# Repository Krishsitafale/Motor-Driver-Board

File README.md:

# TeleOps Motor Driver PCB
### International Rover Challenge (IRC) 2026 | Team Vishwa, VJTI

## Overview

The **TeleOps Motor Driver PCB** is a custom-designed embedded motor control board developed for **Team Vishwa, VJTI** for the **International Rover Challenge (IRC) 2026**.

The objective of this board was to consolidate multiple motor driver modules, PWM generators, power regulators, and peripheral interfaces into a single reliable PCB capable of controlling the rover's complete teleoperation subsystem.

Unlike conventional rover electronics that rely on several separate modules connected with extensive wiring, this PCB integrates all essential electronics into one compact system, improving reliability, reducing wiring complexity, and simplifying maintenance during competitions.

## Features

- ESP32-S3 based control unit
- Custom 5V Buck Converter (TPS54302)
- 10 High Current H-Bridge Drivers (BTN9970LV)
- PCA9685 16-Channel PWM Expander
- Encoder Interfaces
- GPS Interface
- Servo Motor Support
- Modular Connectors
- High Current PCB Layout
- Designed specifically for IRC Rover

## Hardware Specifications

| Component | Description |
|-----------|-------------|
| Microcontroller | ESP32-S3 |
| Buck Converter | TPS54302 |
| Motor Driver  | BTN9970LV |
| PWM Expansion | PCA9685 |
| Logic Voltage | 3.3V |
| Motor Supply  | 12V |
| PCB | 2 Layer |
| Communication | I²C, GPIO, PWM |

# System Architecture

                         12V Battery
                              │
                ┌─────────────┴─────────────┐
                │                           │
                │                    Motor Supply
                │                           │
                ▼                           ▼
      TPS54302 Buck Converter      10× BTN9970LV Drivers
                │
                ▼
             5V Rail
                │
                ▼
           ESP32-S3 MCU
                │
      ┌─────────┼─────────────────────────────┐
      │         │                             │
      │         │ I²C                         │ Native PWM
      │         ▼                             ▼
      │     PCA9685                    ESP32 PWM Outputs
      │   (16 Channel PWM)             (LEDC Peripheral)
      │         │                             │
      │         │                             ├──────── 2 DC Motor Drivers
      │         │                             │
      │         │                             └──────── 4 Servo Motors
      │         │
      │         ├──────── 8 Motor Driver PWM Inputs
      │         │
      │         └──────── Future Expansion
      │
      ├──────── Encoder Inputs
      │
      ├──────── GPS Interface
      │
      └──────── Programming Interface

## Motor Control Architecture

The rover requires control of multiple actuators with independent PWM channels. To efficiently utilize the ESP32's peripherals, the PWM generation is divided as follows:

| PWM Source | Devices Controlled |
|------------|--------------------|
| PCA9685(PWM Expander) | 8 High-Power DC Motor Drivers |
| ESP32 Native PWM      | 2 High-Power DC Motor Drivers |
| ESP32 Native PWM      | 4 Servo Motors                |

This hybrid architecture reduces the processing load on the ESP32 while providing highly stable PWM signals for the drivetrain and robotic arm.

## Supported Actuators

### Drive System

- 6 Planetary DC Motors

### Robotic Arm

- 3 Stepper Motors
- 1 Planetary DC Motor
- 2 Worm Gear Motors
- 4 Servo Motors

### Sensors

- OE775 Quadrature Encoders
- GPS Module

## PCB Highlights

- Dedicated power plane for motor supply
- Optimized ground routing
- High-current copper traces
- Decoupling for every IC
- Modular connector layout
- Compact footprint
- Easy debugging headers
- Competition-ready wiring

## Testing

The PCB has successfully passed the following validation tests.

- Power Supply Verification
- ESP32 Programming
- Buck Converter Efficiency Test
- PCA9685 Communication
- PWM Signal Verification
- Motor Driver Validation
- Encoder Testing
- Servo Testing
- Thermal Performance
- Complete System Integration

## Future Improvements

- Closed Loop Motor Control
- Current Monitoring
- Battery Voltage Monitoring
- CAN Bus Support
- IMU Integration
- OTA Firmware Updates
- ROS 2 Compatibility

## Gallery

## Acknowledgements

This PCB was designed and developed as part of the **Electronics Subsystem** of **Team Vishwa, VJTI** for the **International Rover Challenge (IRC) 2026**.

Special thanks to **Atharva Khare** for his invaluable guidance throughout the design, debugging, and testing phases of the project.

## Author

**Krish Sitafale**

Electronics & Telecommunication Engineering  
Veermata Jijabai Technological Institute (VJTI), Mumbai

Team Vishwa – IRC 2026

## License

This project is released for educational and research purposes.

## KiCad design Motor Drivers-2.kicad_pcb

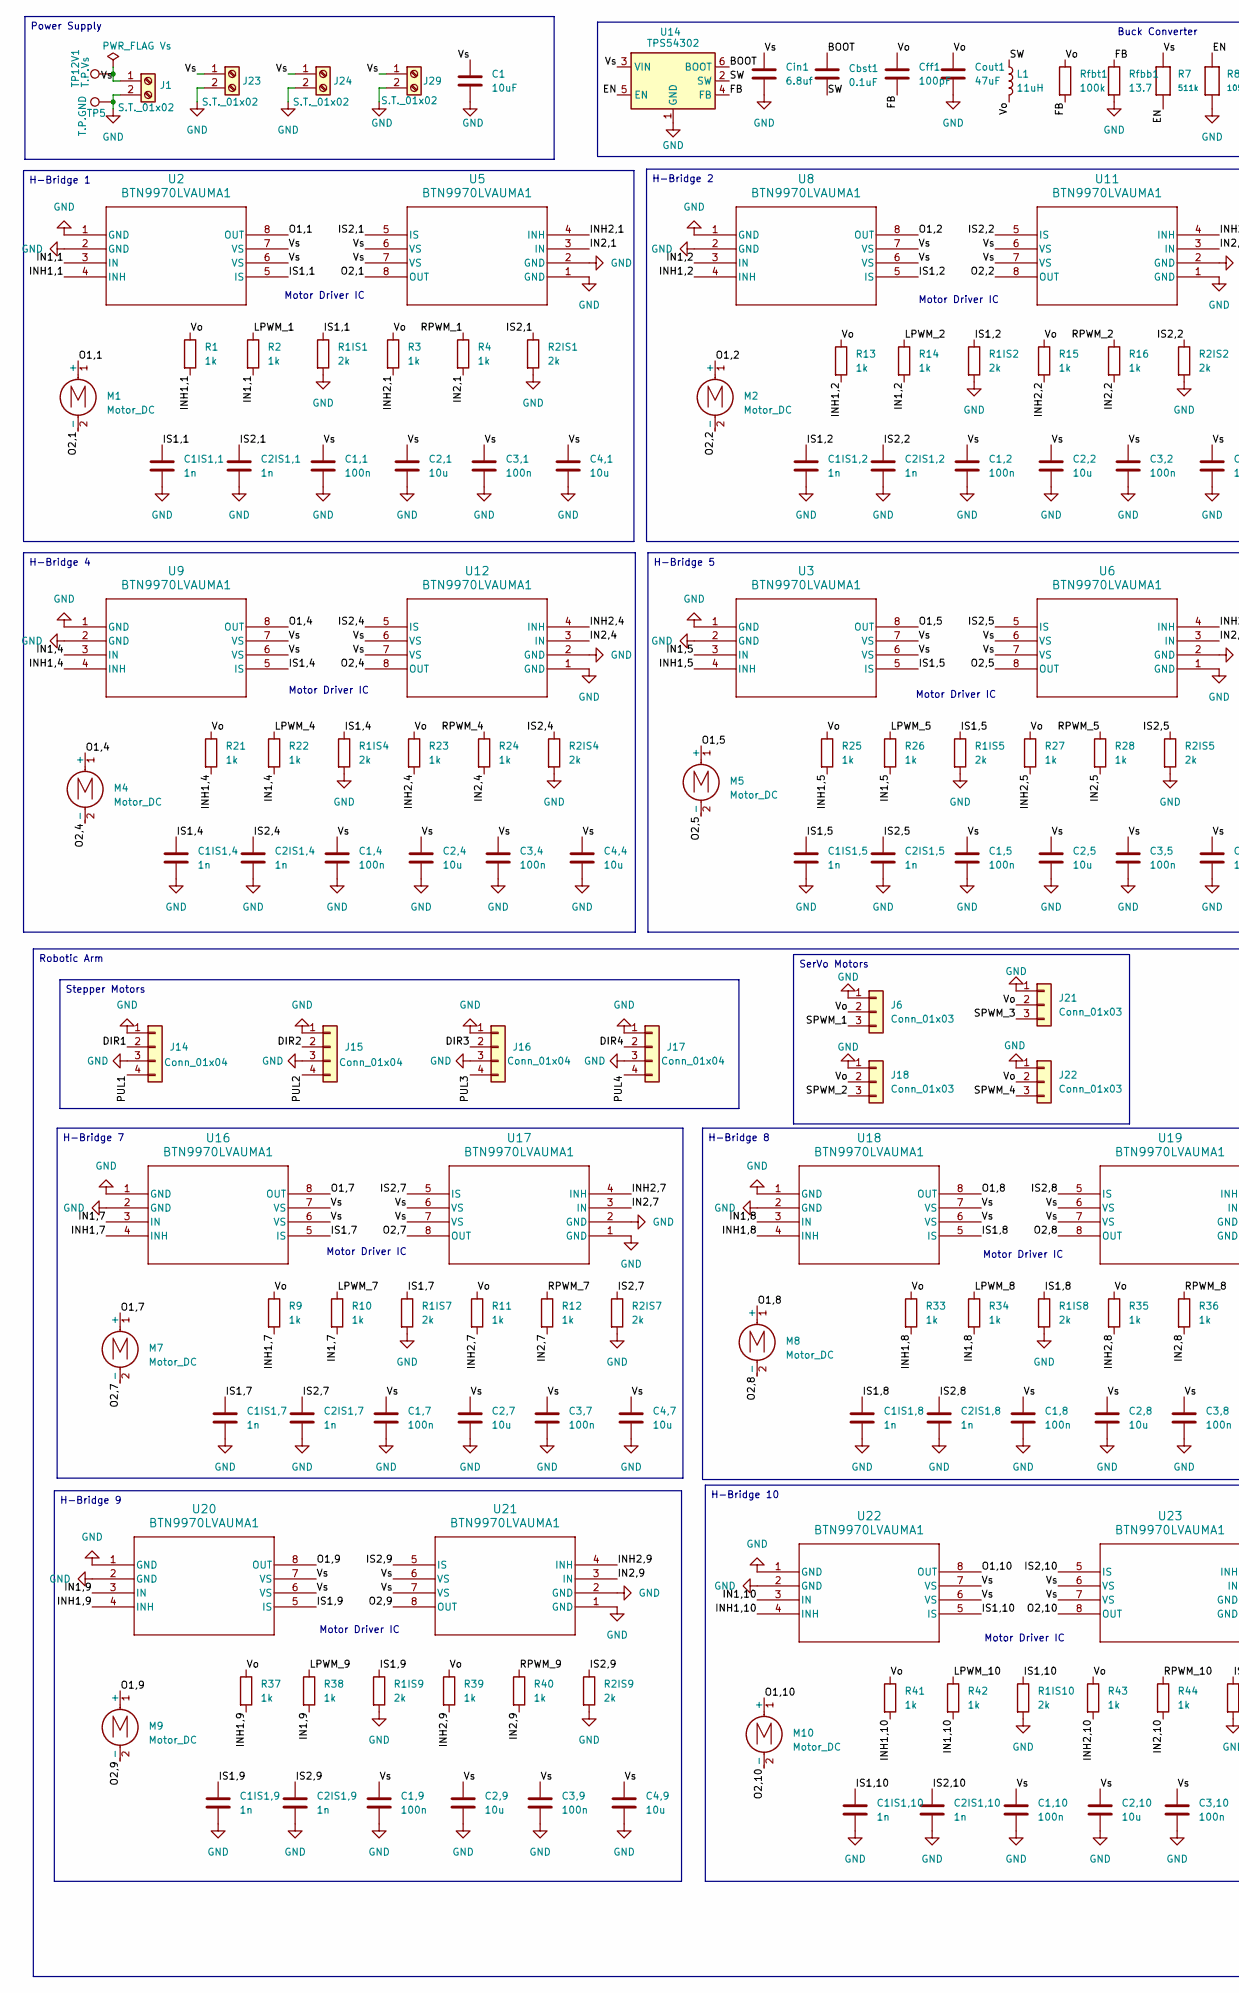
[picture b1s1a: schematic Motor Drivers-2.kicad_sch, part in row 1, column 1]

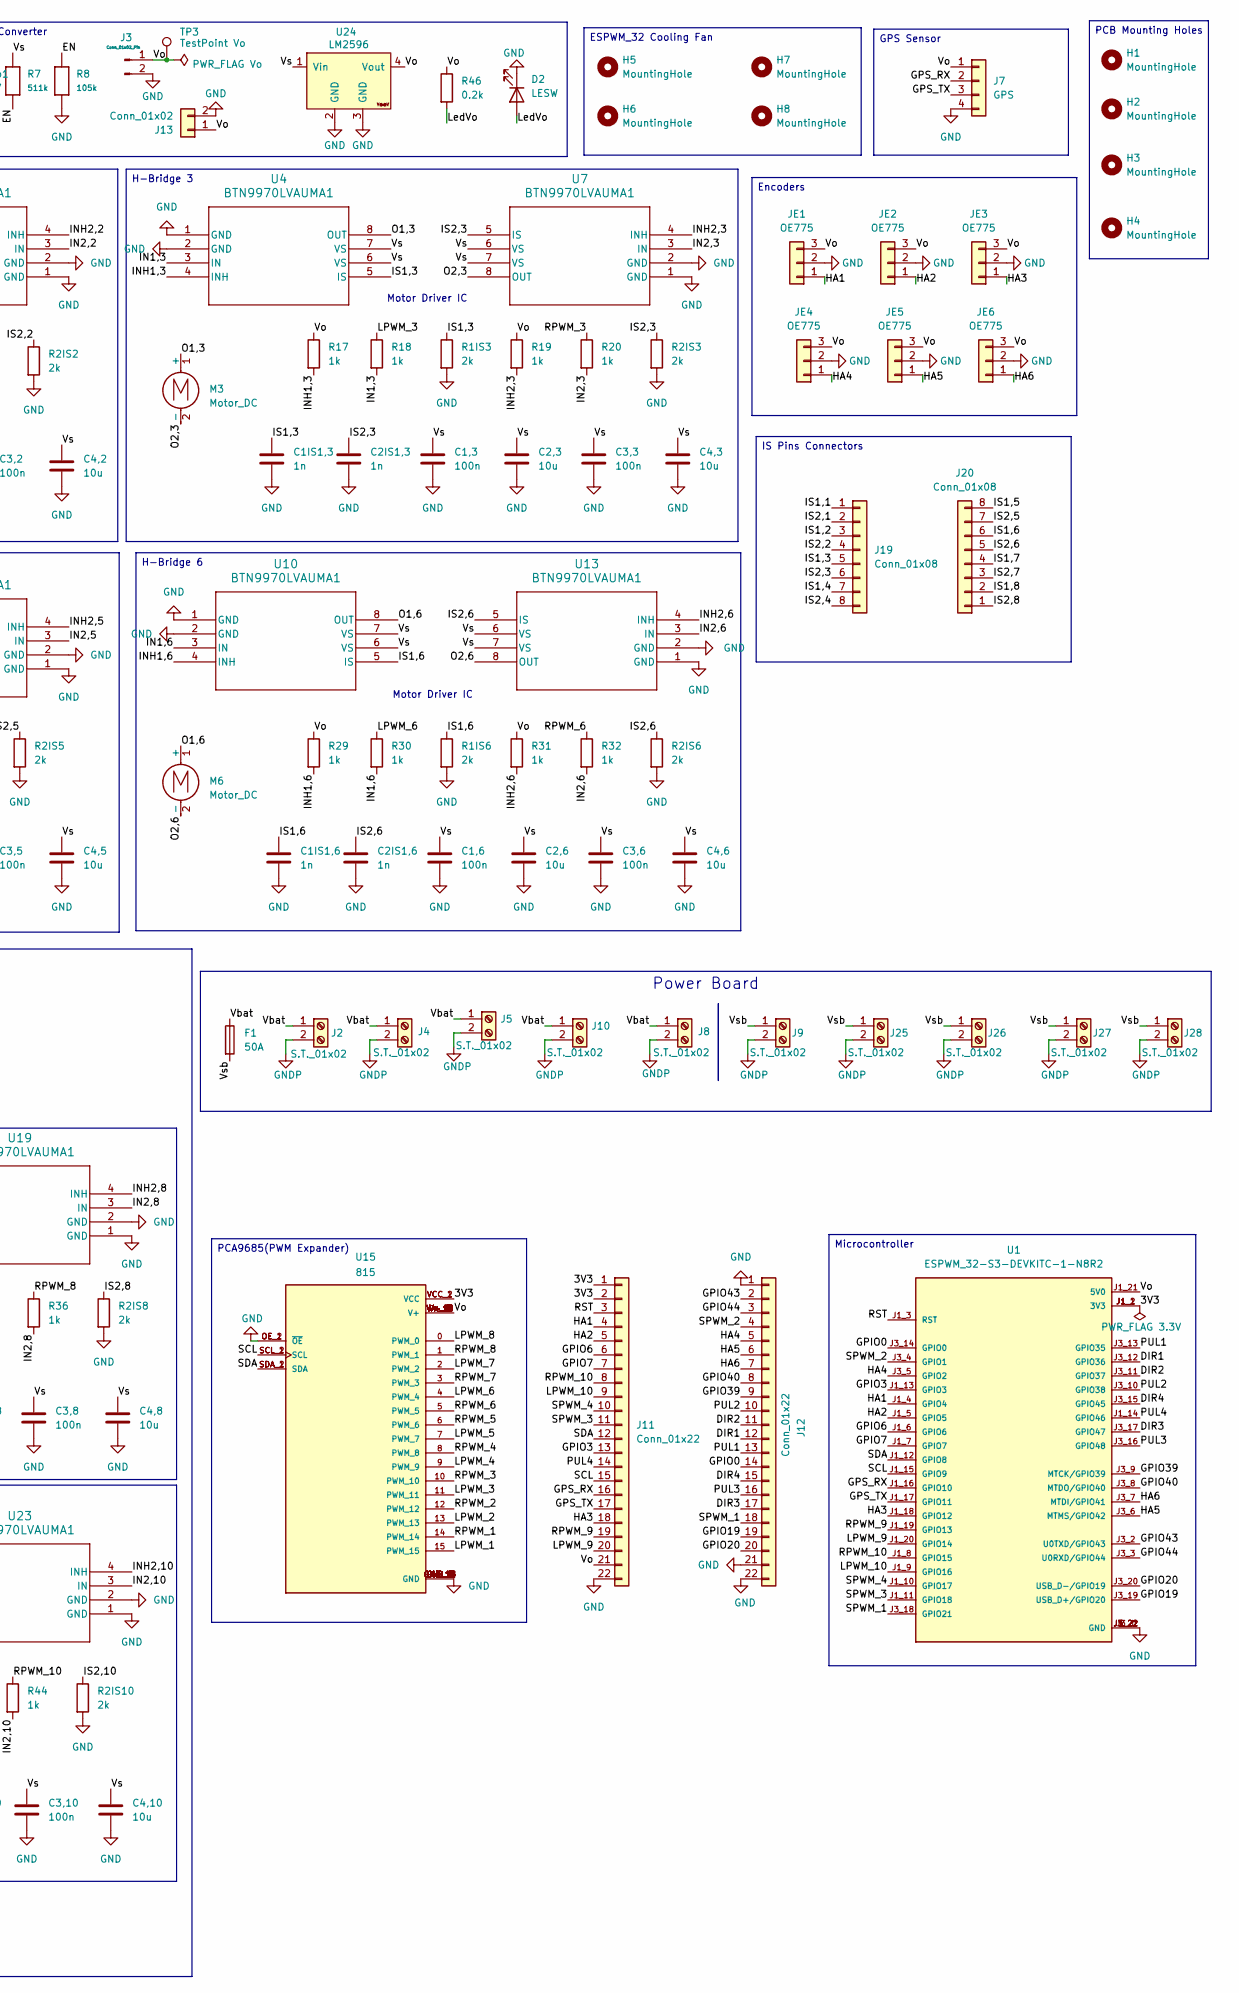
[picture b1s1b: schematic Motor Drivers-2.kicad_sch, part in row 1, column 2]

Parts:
C1: 10uF; C_Radial_D10.0mm_H12.5mm_P5.00mm
C1,1, C1,2, C1,3, C1,4, C1,5, C1,6, C1,7, C1,8, C1,9, C1,10, C3,1, C3,2, C3,3, C3,4, C3,5, C3,6, C3,7, C3,8, C3,9, C3,10: 100n; C_0805_2012Metric_Pad1.18x1.45mm_HandSolder
C1IS1,1, C1IS1,2, C1IS1,3, C1IS1,4, C1IS1,5, C1IS1,6, C1IS1,7, C1IS1,8, C1IS1,9, C1IS1,10, C2IS1,1, C2IS1,2, C2IS1,3, C2IS1,4, C2IS1,5, C2IS1,6, C2IS1,7, C2IS1,8, C2IS1,9, C2IS1,10: 1n; C_0805_2012Metric_Pad1.18x1.45mm_HandSolder
C2,1, C2,2, C2,3, C2,4, C2,5, C2,6, C2,7, C2,8, C2,9, C2,10, C4,1, C4,2, C4,3, C4,4, C4,5, C4,6, C4,7, C4,8, C4,9, C4,10: 10u; C_1210_3225Metric_Pad1.33x2.70mm_HandSolder
Cbst1: 0.1uF; C_0805_2012Metric
Cff1: 100pF; C_0805_2012Metric
Cin1: 6.8uf; C_1812_4532Metric_Pad1.57x3.40mm_HandSolder
Cout1: 47uF; C_1210_3225Metric_Pad1.33x2.70mm_HandSolder
D2: LESW; LED_0805_2012Metric_Pad1.15x1.40mm_HandSolder
F1: 50A; TerminalBlock_Altech_AK300-2_P5.00mm
H1, H2, H3, H4: MountingHole; MountingHole_4.3mm_M4
H5, H6, H7, H8: MountingHole; MountingHole_2mm
J1, J2, J4, J5, J8, J9, J10, J23, J24, J25, J26, J27, J28, J29: S.T._01x02; AMASS_XT60-M_1x02_P7.20mm_Vertical
J3: Conn_01x02_Pin; JST_XH_B2B-XH-A_1x02_P2.50mm_Vertical
J6, J18, J21, J22: Conn_01x03; JST_XH_B3B-XH-A_1x03_P2.50mm_Vertical
J7: GPS; JST_XH_B4B-XH-A_1x04_P2.50mm_Vertical
J11, J12: Conn_01x22; PinHeader_1x22_P2.54mm_Vertical
J13: Conn_01x02; JST_XH_B2B-XH-A_1x02_P2.50mm_Vertical
J14, J15, J16, J17: Conn_01x04; JST_XH_B4B-XH-A_1x04_P2.50mm_Vertical
J19, J20: Conn_01x08; JST_XH_B8B-XH-A_1x08_P2.50mm_Vertical
JE1, JE2, JE3, JE4, JE5, JE6: OE775; JST_XH_B3B-XH-A_1x03_P2.50mm_Vertical
L1: 11uH; L_Wuerth_HCM-1052
M1, M2, M3, M4, M5, M6, M7, M8, M9, M10: Motor_DC; AMASS_XT60-M_1x02_P7.20mm_Vertical
R1, R2, R3, R4, R9, R10, R11, R12, R13, R14, R15, R16, R17, R18, R19, R20, R21, R22, R23, R24, R25, R26, R27, R28, R29, R30, R31, R32, R33, R34, R35, R36, R37, R38, R39, R40, R41, R42, R43, R44: 1k; R_0805_2012Metric_Pad1.20x1.40mm_HandSolder
R1IS1, R1IS2, R1IS3, R1IS4, R1IS5, R1IS6, R1IS7, R1IS8, R1IS9, R1IS10, R2IS1, R2IS2, R2IS3, R2IS4, R2IS5, R2IS6, R2IS7, R2IS8, R2IS9, R2IS10: 2k; R_0805_2012Metric_Pad1.20x1.40mm_HandSolder
R7: 511k; R_0805_2012Metric_Pad1.20x1.40mm_HandSolder
R8: 105k; R_0805_2012Metric_Pad1.20x1.40mm_HandSolder
R46: 0.2k; R_0805_2012Metric_Pad1.20x1.40mm_HandSolder
Rfbb1: 13.7; R_0805_2012Metric
Rfbt1: 100k; R_0805_2012Metric
TP3: TestPoint Vo; TestPoint_Pad_D1.5mm
TP5: T.P.GND; TestPoint_Pad_D1.5mm
TP12V1: T.P.Vs; TestPoint_Pad_D1.5mm
U1: ESPWM_32-S3-DEVKITC-1-N8R2; XCVR_ESP32-S3-DEVKITC-1-N8R2; PARTREV V1
U2, U3, U4, U5, U6, U7, U8, U9, U10, U11, U12, U13, U16, U17, U18, U19, U20, U21, U22, U23: BTN9970LVAUMA1; IFX-PG-HSOF-7-1-V
U14: TPS54302; SOT-23-6
U15: 815; MODULE_815; PARTREV C
U24: LM2596; YAAJ_DCDC_StepDown_LM2596

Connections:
/3V3: J11.1, J11.2, U1.J1_1 (3V3), U1.J1_2 (3V3), U15.VCC_1 (VCC), U15.VCC_2 (VCC)
/BOOT: Cbst1.1, U14.6 (BOOT)
/DIR1: J12.12, J14.2, U1.J3_12 (GPIO36)
/DIR2: J12.11, J15.2, U1.J3_11 (GPIO37)
/DIR3: J12.17, J16.2, U1.J3_17 (GPIO47)
/DIR4: J12.15, J17.2, U1.J3_15 (GPIO45)
/EN: R7.1, R8.2, U14.5 (EN)
/FB: Cff1.2, Rfbb1.1, Rfbt1.2, U14.4 (FB)
/GPIO0: J12.14, U1.J3_14 (GPIO0)
/GPIO3: J11.13, U1.J1_13 (GPIO3)
/GPIO6: J11.6, U1.J1_6 (GPIO6)
/GPIO7: J11.7, U1.J1_7 (GPIO7)
/GPIO19: J12.19, U1.J3_19 (USB_D+/GPIO20)
/GPIO20: J12.20, U1.J3_20 (USB_D-/GPIO19)
/GPIO39: J12.9, U1.J3_9 (MTCK/GPIO39)
/GPIO40: J12.8, U1.J3_8 (MTDO/GPIO40)
/GPIO43: J12.2, U1.J3_2 (U0TXD/GPIO43)
/GPIO44: J12.3, U1.J3_3 (U0RXD/GPIO44)
/GPS_RX: J7.2, J11.16, U1.J1_16 (GPIO10)
/GPS_TX: J7.3, J11.17, U1.J1_17 (GPIO11)
/HA1: J11.4, JE1.1, U1.J1_4 (GPIO4)
/HA2: J11.5, JE2.1, U1.J1_5 (GPIO5)
/HA3: J11.18, JE3.1, U1.J1_18 (GPIO12)
/HA4: J12.5, JE4.1, U1.J3_5 (GPIO2)
/HA5: J12.6, JE5.1, U1.J3_6 (MTMS/GPIO42)
/HA6: J12.7, JE6.1, U1.J3_7 (MTDI/GPIO41)
/IN1,1: R2.2, U2.3 (IN)
/IN1,2: R14.2, U8.3 (IN)
/IN1,3: R18.2, U4.3 (IN)
/IN1,4: R22.2, U9.3 (IN)
/IN1,5: R26.2, U3.3 (IN)
/IN1,6: R30.2, U10.3 (IN)
/IN1,7: R10.2, U16.3 (IN)
/IN1,8: R34.2, U18.3 (IN)
/IN1,9: R38.2, U20.3 (IN)
/IN1,10: R42.2, U22.3 (IN)
/IN2,1: R4.2, U5.3 (IN)
/IN2,2: R16.2, U11.3 (IN)
/IN2,3: R20.2, U7.3 (IN)
/IN2,4: R24.2, U12.3 (IN)
/IN2,5: R28.2, U6.3 (IN)
/IN2,6: R32.2, U13.3 (IN)
/IN2,7: R12.2, U17.3 (IN)
/IN2,8: R36.2, U19.3 (IN)
/IN2,9: R40.2, U21.3 (IN)
/IN2,10: R44.2, U23.3 (IN)
/INH1,1: R1.2, U2.4 (INH)
/INH1,2: R13.2, U8.4 (INH)
/INH1,3: R17.2, U4.4 (INH)
/INH1,4: R21.2, U9.4 (INH)
/INH1,5: R25.2, U3.4 (INH)
/INH1,6: R29.2, U10.4 (INH)
/INH1,7: R9.2, U16.4 (INH)
/INH1,8: R33.2, U18.4 (INH)
/INH1,9: R37.2, U20.4 (INH)
/INH1,10: R41.2, U22.4 (INH)
/INH2,1: R3.2, U5.4 (INH)
/INH2,2: R15.2, U11.4 (INH)
/INH2,3: R19.2, U7.4 (INH)
/INH2,4: R23.2, U12.4 (INH)
/INH2,5: R27.2, U6.4 (INH)
/INH2,6: R31.2, U13.4 (INH)
/INH2,7: R11.2, U17.4 (INH)
/INH2,8: R35.2, U19.4 (INH)
/INH2,9: R39.2, U21.4 (INH)
/INH2,10: R43.2, U23.4 (INH)
/IS1,1: C1IS1,1.1, J19.1, R1IS1.1, U2.5 (IS)
/IS1,2: C1IS1,2.1, J19.3, R1IS2.1, U8.5 (IS)
/IS1,3: C1IS1,3.1, J19.5, R1IS3.1, U4.5 (IS)
/IS1,4: C1IS1,4.1, J19.7, R1IS4.1, U9.5 (IS)
/IS1,5: C1IS1,5.1, J20.8, R1IS5.1, U3.5 (IS)
/IS1,6: C1IS1,6.1, J20.6, R1IS6.1, U10.5 (IS)
/IS1,7: C1IS1,7.1, J20.4, R1IS7.1, U16.5 (IS)
/IS1,8: C1IS1,8.1, J20.2, R1IS8.1, U18.5 (IS)
/IS1,9: C1IS1,9.1, R1IS9.1, U20.5 (IS)
/IS1,10: C1IS1,10.1, R1IS10.1, U22.5 (IS)
/IS2,1: C2IS1,1.1, J19.2, R2IS1.1, U5.5 (IS)
/IS2,2: C2IS1,2.1, J19.4, R2IS2.1, U11.5 (IS)
/IS2,3: C2IS1,3.1, J19.6, R2IS3.1, U7.5 (IS)
/IS2,4: C2IS1,4.1, J19.8, R2IS4.1, U12.5 (IS)
/IS2,5: C2IS1,5.1, J20.7, R2IS5.1, U6.5 (IS)
/IS2,6: C2IS1,6.1, J20.5, R2IS6.1, U13.5 (IS)
/IS2,7: C2IS1,7.1, J20.3, R2IS7.1, U17.5 (IS)
/IS2,8: C2IS1,8.1, J20.1, R2IS8.1, U19.5 (IS)
/IS2,9: C2IS1,9.1, R2IS9.1, U21.5 (IS)
/IS2,10: C2IS1,10.1, R2IS10.1, U23.5 (IS)
/LPWM_1: R2.1, U15.15 (PWM_15)
/LPWM_2: R14.1, U15.13 (PWM_13)
/LPWM_3: R18.1, U15.11 (PWM_11)
/LPWM_4: R22.1, U15.9 (PWM_9)
/LPWM_5: R26.1, U15.7 (PWM_7)
/LPWM_6: R30.1, U15.4 (PWM_4)
/LPWM_7: R10.1, U15.2 (PWM_2)
/LPWM_8: R34.1, U15.0 (PWM_0)
/LPWM_9: J11.20, R38.1, U1.J1_20 (GPIO14)
/LPWM_10: J11.9, R42.1, U1.J1_9 (GPIO16)
/LedVo: D2.2 (A), R46.2
/O1,1: M1.1 (+), U2.8 (OUT)
/O1,2: M2.1 (+), U8.8 (OUT)
/O1,3: M3.1 (+), U4.8 (OUT)
/O1,4: M4.1 (+), U9.8 (OUT)
/O1,5: M5.1 (+), U3.8 (OUT)
/O1,6: M6.1 (+), U10.8 (OUT)
/O1,7: M7.1 (+), U16.8 (OUT)
/O1,8: M8.1 (+), U18.8 (OUT)
/O1,9: M9.1 (+), U20.8 (OUT)
/O1,10: M10.1 (+), U22.8 (OUT)
/O2,1: M1.2 (-), U5.8 (OUT)
/O2,2: M2.2 (-), U11.8 (OUT)
/O2,3: M3.2 (-), U7.8 (OUT)
/O2,4: M4.2 (-), U12.8 (OUT)
/O2,5: M5.2 (-), U6.8 (OUT)
/O2,6: M6.2 (-), U13.8 (OUT)
/O2,7: M7.2 (-), U17.8 (OUT)
/O2,8: M8.2 (-), U19.8 (OUT)
/O2,9: M9.2 (-), U21.8 (OUT)
/O2,10: M10.2 (-), U23.8 (OUT)
/PUL1: J12.13, J14.4, U1.J3_13 (GPIO35)
/PUL2: J12.10, J15.4, U1.J3_10 (GPIO38)
/PUL3: J12.16, J16.4, U1.J3_16 (GPIO48)
/PUL4: J11.14, J17.4, U1.J1_14 (GPIO46)
/RPWM_1: R4.1, U15.14 (PWM_14)
/RPWM_2: R16.1, U15.12 (PWM_12)
/RPWM_3: R20.1, U15.10 (PWM_10)
/RPWM_4: R24.1, U15.8 (PWM_8)
/RPWM_5: R28.1, U15.6 (PWM_6)
/RPWM_6: R32.1, U15.5 (PWM_5)
/RPWM_7: R12.1, U15.3 (PWM_3)
/RPWM_8: R36.1, U15.1 (PWM_1)
/RPWM_9: J11.19, R40.1, U1.J1_19 (GPIO13)
/RPWM_10: J11.8, R44.1, U1.J1_8 (GPIO15)
/RST: J11.3, U1.J1_3 (RST)
/SCL: J11.15, U1.J1_15 (GPIO9), U15.SCL_1 (SCL), U15.SCL_2 (SCL)
/SDA: J11.12, U1.J1_12 (GPIO8), U15.SDA_1 (SDA), U15.SDA_2 (SDA)
/SPWM_1: J6.3, J12.18, U1.J3_18 (GPIO21)
/SPWM_2: J12.4, J18.3, U1.J3_4 (GPIO1)
/SPWM_3: J11.11, J21.3, U1.J1_11 (GPIO18)
/SPWM_4: J11.10, J22.3, U1.J1_10 (GPIO17)
/SW: Cbst1.2, L1.1, U14.2 (SW)
/Vbat: F1.1, J2.1, J4.1, J5.1, J8.1, J10.1
/Vo: Cff1.1, Cout1.1, J3.1, J6.2, J7.1, J11.21, J13.1, J18.2, J21.2, J22.2, JE1.3, JE2.3, JE3.3, JE4.3, JE5.3, JE6.3, L1.2, R1.1, R3.1, R9.1, R11.1, R13.1, R15.1, R17.1, R19.1, R21.1, R23.1, R25.1, R27.1, R29.1, R31.1, R33.1, R35.1, R37.1, R39.1, R41.1, R43.1, R46.1, Rfbt1.1, TP3.1, U1.J1_21 (5V0), U15.V+_1 (V+), U15.V+_2 (V+), U15.V+_3 (V+), U15.V+_4 (V+), U15.V+_5 (V+), U15.V+_6 (V+), U15.V+_7 (V+), U15.V+_8 (V+), U15.V+_9 (V+), U15.V+_10 (V+), U15.V+_11 (V+), U15.V+_12 (V+), U15.V+_13 (V+), U15.V+_14 (V+), U15.V+_15 (V+), U15.V+_16 (V+), U15.V+_17 (V+), U15.V+_18 (V+), U24.4 (Vout)
/Vs: C1.1, C1,1.1, C1,2.1, C1,3.1, C1,4.1, C1,5.1, C1,6.1, C1,7.1, C1,8.1, C1,9.1, C1,10.1, C2,1.1, C2,2.1, C2,3.1, C2,4.1, C2,5.1, C2,6.1, C2,7.1, C2,8.1, C2,9.1, C2,10.1, C3,1.1, C3,2.1, C3,3.1, C3,4.1, C3,5.1, C3,6.1, C3,7.1, C3,8.1, C3,9.1, C3,10.1, C4,1.1, C4,2.1, C4,3.1, C4,4.1, C4,5.1, C4,6.1, C4,7.1, C4,8.1, C4,9.1, C4,10.1, Cin1.1, J1.1, J23.1, J24.1, J29.1, R7.2, TP12V1.1, U2.6 (VS), U2.7 (VS), U3.6 (VS), U3.7 (VS), U4.6 (VS), U4.7 (VS), U5.6 (VS), U5.7 (VS), U6.6 (VS), U6.7 (VS), U7.6 (VS), U7.7 (VS), U8.6 (VS), U8.7 (VS), U9.6 (VS), U9.7 (VS), U10.6 (VS), U10.7 (VS), U11.6 (VS), U11.7 (VS), U12.6 (VS), U12.7 (VS), U13.6 (VS), U13.7 (VS), U14.3 (VIN), U16.6 (VS), U16.7 (VS), U17.6 (VS), U17.7 (VS), U18.6 (VS), U18.7 (VS), U19.6 (VS), U19.7 (VS), U20.6 (VS), U20.7 (VS), U21.6 (VS), U21.7 (VS), U22.6 (VS), U22.7 (VS), U23.6 (VS), U23.7 (VS), U24.1 (Vin)
/Vsb: F1.2, J9.1, J25.1, J26.1, J27.1, J28.1
GND: C1.2, C1,1.2, C1,2.2, C1,3.2, C1,4.2, C1,5.2, C1,6.2, C1,7.2, C1,8.2, C1,9.2, C1,10.2, C1IS1,1.2, C1IS1,2.2, C1IS1,3.2, C1IS1,4.2, C1IS1,5.2, C1IS1,6.2, C1IS1,7.2, C1IS1,8.2, C1IS1,9.2, C1IS1,10.2, C2,1.2, C2,2.2, C2,3.2, C2,4.2, C2,5.2, C2,6.2, C2,7.2, C2,8.2, C2,9.2, C2,10.2, C2IS1,1.2, C2IS1,2.2, C2IS1,3.2, C2IS1,4.2, C2IS1,5.2, C2IS1,6.2, C2IS1,7.2, C2IS1,8.2, C2IS1,9.2, C2IS1,10.2, C3,1.2, C3,2.2, C3,3.2, C3,4.2, C3,5.2, C3,6.2, C3,7.2, C3,8.2, C3,9.2, C3,10.2, C4,1.2, C4,2.2, C4,3.2, C4,4.2, C4,5.2, C4,6.2, C4,7.2, C4,8.2, C4,9.2, C4,10.2, Cin1.2, Cout1.2, D2.1 (K), J1.2, J3.2, J6.1, J7.4, J11.22, J12.1, J12.21, J12.22, J13.2, J14.1, J14.3, J15.1, J15.3, J16.1, J16.3, J17.1, J17.3, J18.1, J21.1, J22.1, J23.2, J24.2, J29.2, JE1.2, JE2.2, JE3.2, JE4.2, JE5.2, JE6.2, R1IS1.2, R1IS2.2, R1IS3.2, R1IS4.2, R1IS5.2, R1IS6.2, R1IS7.2, R1IS8.2, R1IS9.2, R1IS10.2, R2IS1.2, R2IS2.2, R2IS3.2, R2IS4.2, R2IS5.2, R2IS6.2, R2IS7.2, R2IS8.2, R2IS9.2, R2IS10.2, R8.1, Rfbb1.2, TP5.1, U1.J1_22 (GND), U1.J3_1 (GND), U1.J3_21 (GND), U1.J3_22 (GND), U2.1 (GND), U2.2 (GND), U3.1 (GND), U3.2 (GND), U4.1 (GND), U4.2 (GND), U5.1 (GND), U5.2 (GND), U6.1 (GND), U6.2 (GND), U7.1 (GND), U7.2 (GND), U8.1 (GND), U8.2 (GND), U9.1 (GND), U9.2 (GND), U10.1 (GND), U10.2 (GND), U11.1 (GND), U11.2 (GND), U12.1 (GND), U12.2 (GND), U13.1 (GND), U13.2 (GND), U14.1 (GND), U15.GND_1 (GND), U15.GND_2 (GND), U15.GND_3 (GND), U15.GND_4 (GND), U15.GND_5 (GND), U15.GND_6 (GND), U15.GND_7 (GND), U15.GND_8 (GND), U15.GND_9 (GND), U15.GND_10 (GND), U15.GND_11 (GND), U15.GND_12 (GND), U15.GND_13 (GND), U15.GND_14 (GND), U15.GND_15 (GND), U15.GND_16 (GND), U15.GND_17 (GND), U15.GND_18 (GND), U15.OE_1 (~OE), U15.OE_2 (~OE), U16.1 (GND), U16.2 (GND), U17.1 (GND), U17.2 (GND), U18.1 (GND), U18.2 (GND), U19.1 (GND), U19.2 (GND), U20.1 (GND), U20.2 (GND), U21.1 (GND), U21.2 (GND), U22.1 (GND), U22.2 (GND), U23.1 (GND), U23.2 (GND), U24.2 (GND), U24.3 (GND)
GNDP: J2.2, J4.2, J5.2, J8.2, J9.2, J10.2, J25.2, J26.2, J27.2, J28.2

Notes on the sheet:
Motor Driver IC
H-Bridge 7
H-Bridge 9
H-Bridge 6
Encoders
Microcontroller
SerVo Motors
GPS Sensor
H-Bridge 1
PCB Mounting Holes
H-Bridge 4
Buck Converter
PCA9685(PWM Expander)
H-Bridge 5
ESPWM_32 Cooling Fan
H-Bridge 10
H-Bridge 3
H-Bridge 8
H-Bridge 2
Power Board
Stepper Motors
Robotic Arm
Power Supply
IS Pins Connectors

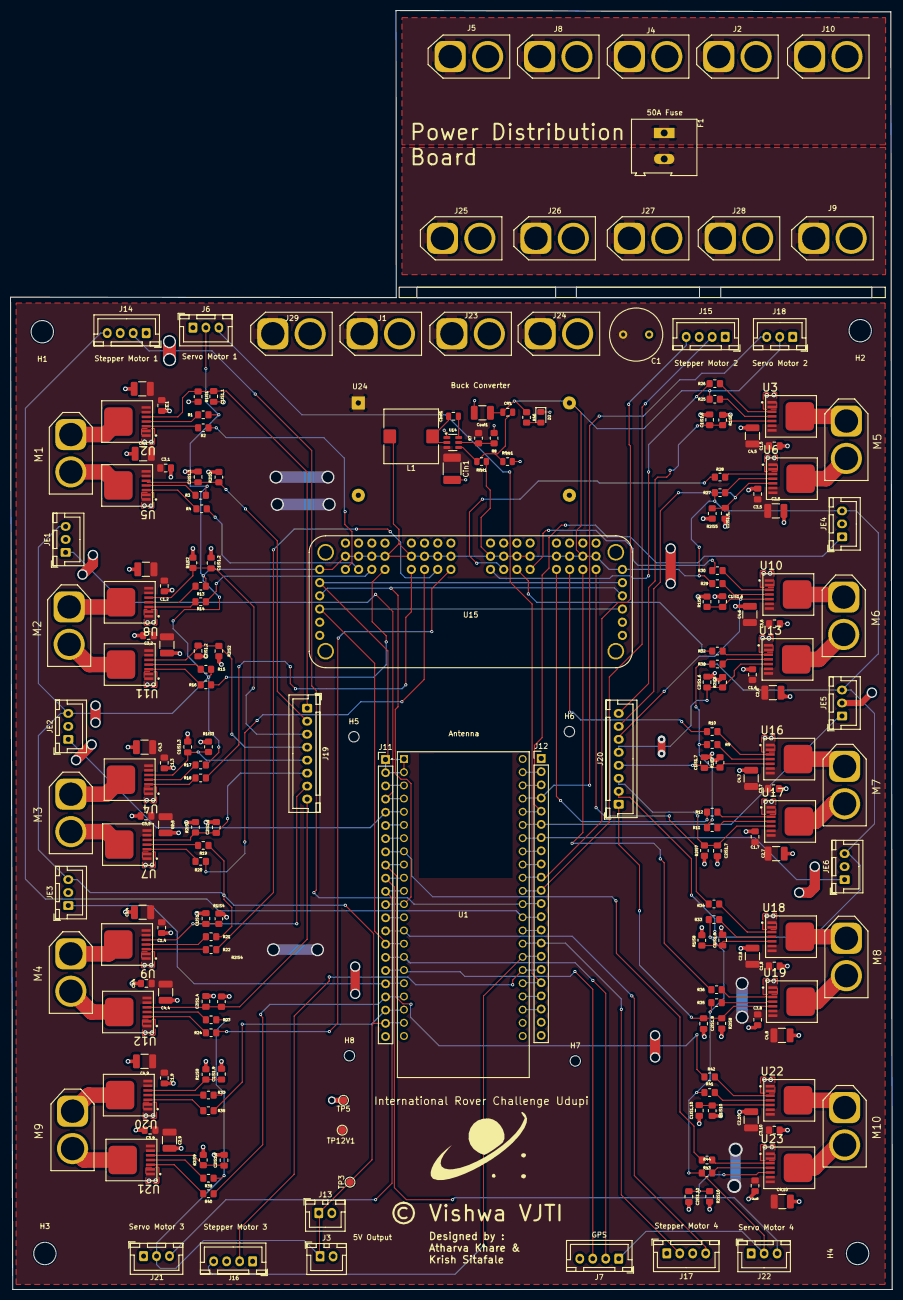
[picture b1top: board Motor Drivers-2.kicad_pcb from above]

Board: 2 copper layers, 169.8 x 246.3 mm, 213 parts (0 on the bottom side), 145 nets.

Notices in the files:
Motor Drivers-2.kicad_pcb:
© Vishwa VJTI
README.md:
License: MIT
